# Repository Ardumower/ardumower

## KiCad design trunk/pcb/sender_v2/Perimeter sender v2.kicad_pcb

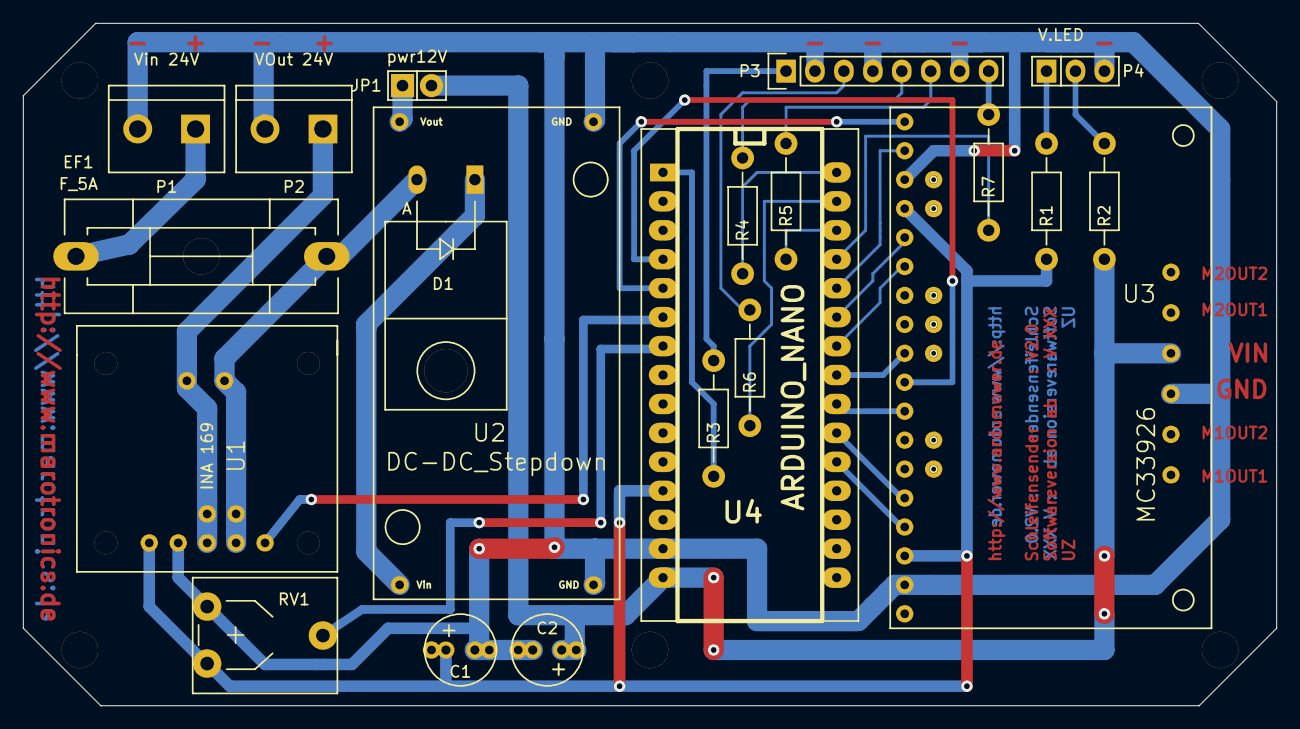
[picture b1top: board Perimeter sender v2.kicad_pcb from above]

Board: 2 copper layers, 110.0 x 59.9 mm, 27 parts (0 on the bottom side), 31 nets.

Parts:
B1, B2, B3, B4, B5, B6: Bohrloch_3,2mm
C1, C2: 100uF; Elko_vert_11.2x6.3mm_RM2.5_RM5.0
D1: MBR 1045; MBR1045_Horizontal
EF1: F_5A; Fuseholder_Reichelt_PL112000
JP1: pwr12V; Pin_Header_Straight_1x02
P1: Vin 24V; Anschlussklemme_2P_RM5,08
P2: VOut 24V; Anschlussklemme_2P_RM5,08
P3: Status LED; Pin_Header_Straight_1x08
P4: V.LED; Pin_Header_Straight_1x03
R1, R3, R4, R5, R6, R7: 220R; Resistor_Horizontal_RM10mm
R2: 560R; Resistor_Horizontal_RM10mm
RV1: POT; Potentiometer_VishaySpectrol-Econtrim-Type36T_3D-angepasst_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
U1: INA 169; INA169
U2: DC-DC_Stepdown; DC_DC_DSN2596_mit_Bohrloch
U3: MC33926; MC_33926_31polig_mit_Bohrloch_neue_Masse
U4: ARDUINO_NANO; arduino_nano

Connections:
+5V: C1.1, R1.1, RV1.3, U1.1, U3.3, U3.15, U4.5V
+12V: C2.1, JP1.2, R2.1, U3.22, U4.VIN
EN: U3.10, U4.D5
GND: C1.2, C2.2, P1.2, P2.2, P3.2, P3.4, P3.7, P4.3, RV1.1, U1.2, U2.1, U2.4, U3.2, U3.16, U3.21, U4.GND1
INA169: U1.3, U4.A2
LED_5V: P4.1, R1.2
LED_12V: P4.2, R2.2
M1FB: U3.9, U4.A0
M1IN1: U3.5, U4.D3
M1IN2: U3.4, U4.D2
M1_DuoLED_Schleife1_Grün: P3.8, R7.1
M1_DuoLED_Schleife1_Rot: P3.6, R5.1
M1nSF: U3.8, U4.D4
M2FB: U3.18, U4.A1
M2IN1: U3.14, U4.D7
M2IN2: U3.13, U4.D6
M2_DuoLED_Schleife2_Grün: P3.3, R6.1
M2_DuoLED_Schleife2_Rot: P3.5, R4.1
M2nSF: U3.17, U4.D8
Mover_in_Ladestation: P3.1, R3.1
unnamed: D1.1, EF1.1, U1.4
unnamed: D1.2, U2.3
unnamed: EF1.2, P1.1
unnamed: JP1.1, U2.2
unnamed: P2.1, U1.5
unnamed: R3.2, U4.D13
unnamed: R4.2, U4.D12
unnamed: R5.2, U4.D10
unnamed: R6.2, U4.D11
unnamed: R7.2, U4.D9
POTI: RV1.2, U4.A3
